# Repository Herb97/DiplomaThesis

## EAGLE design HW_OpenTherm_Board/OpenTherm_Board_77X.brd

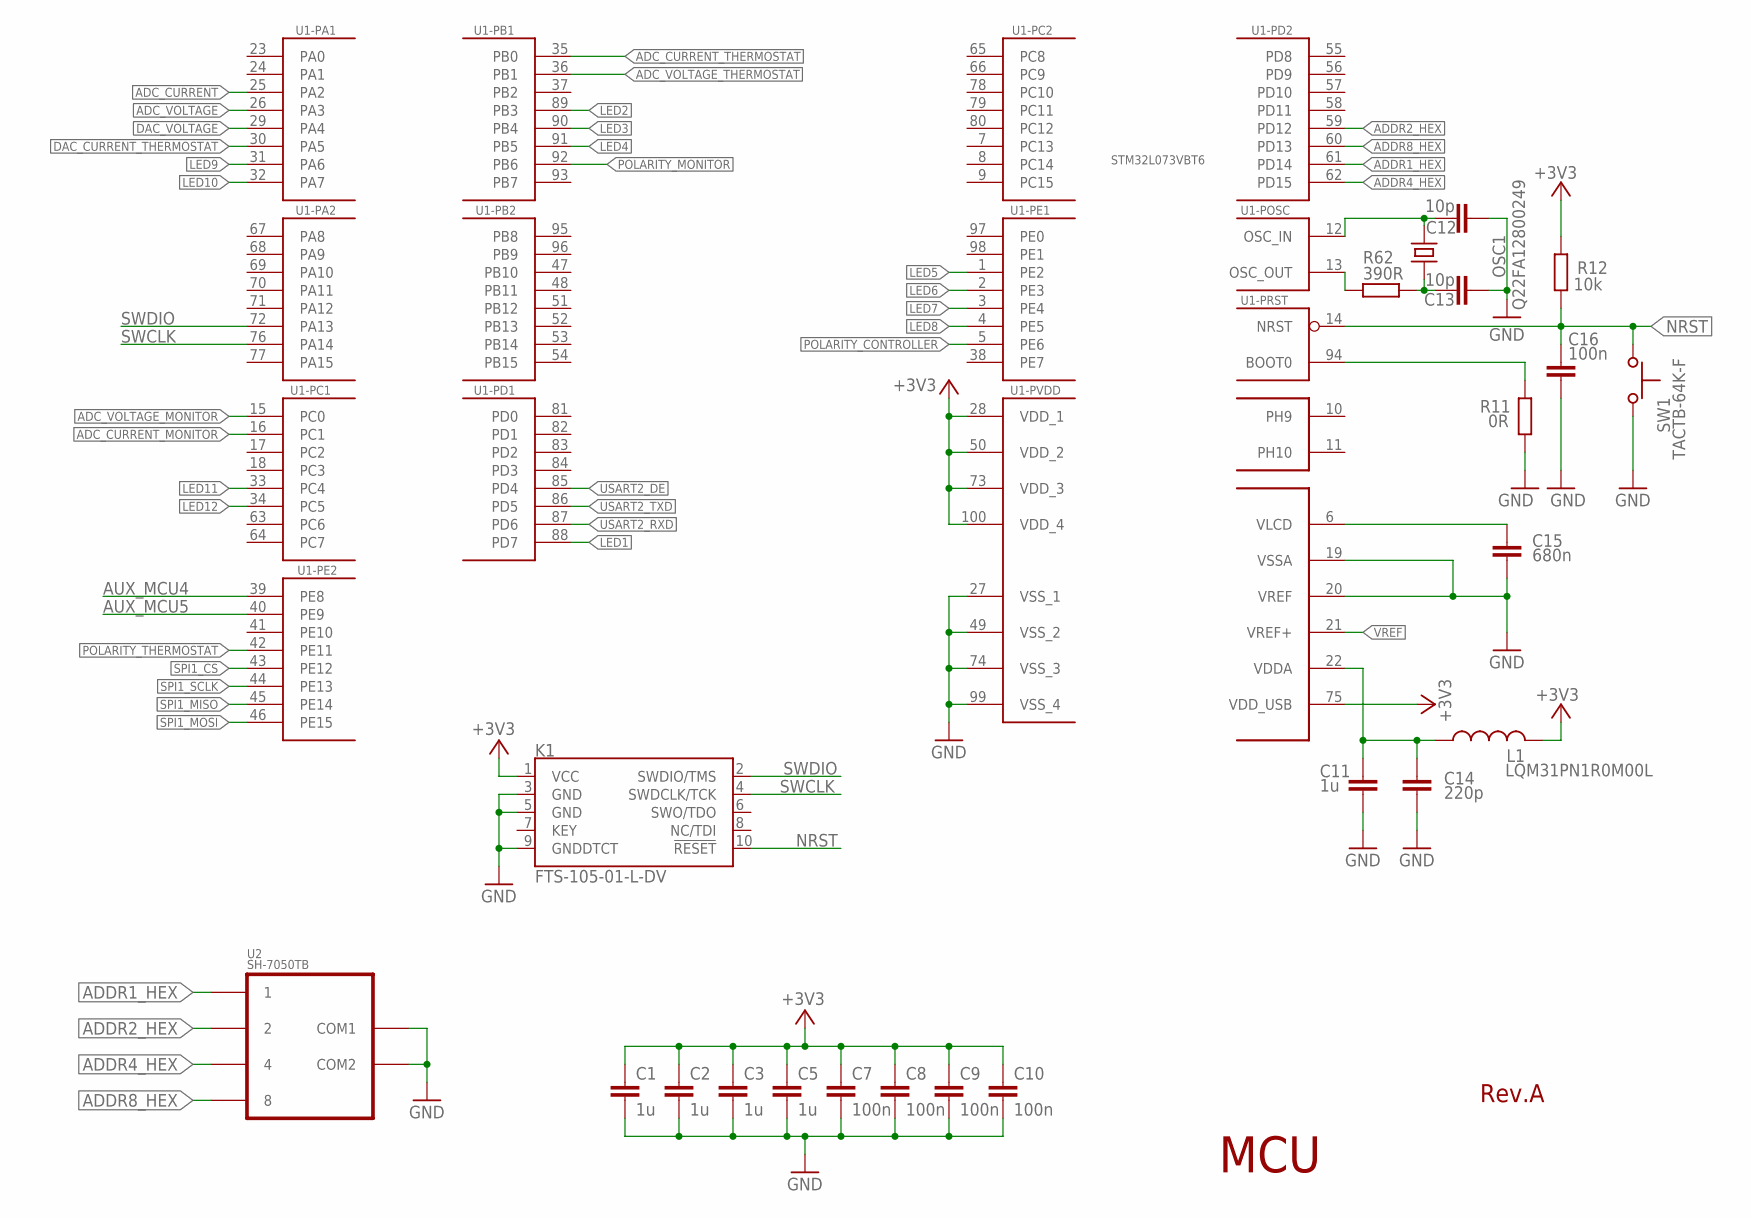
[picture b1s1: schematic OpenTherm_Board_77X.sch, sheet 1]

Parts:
C1, C2, C3, C5, C11: 1u; C0805
C7, C8, C9, C10, C16: 100n; C0603
C12, C13: 10p; C0603
C14: 220p; C0603
C15: 680n; C0603:1
K1: FTS-105-01-L-DV; SAMTECH_FTSH-105-01
L1: LQM31PN1R0M00L; R1206
OSC1: Q22FA12800249; OSCILATOR
R11: 0R; R0603
R12: 10k; R0603
R62: 390R; R0603
SW1: TACTB-64K-F
U1: STM32L073VBT6; TQFP100
U2: SH-7050TB; HEX_DEC

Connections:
+3V3: C1.1, C2.1, C3.1, C5.1, C7.1, C8.1, C9.1, C10.1, K1.1 (VCC), L1.2, R12.2, U1.28 (VDD_1), U1.50 (VDD_2), U1.73 (VDD_3), U1.75 (VDD_USB), U1.100 (VDD_4); also elsewhere on the board
ADC_CURRENT: U1.25 (PA2); also elsewhere on the board
ADC_CURRENT_MONITOR: U1.16 (PC1); also elsewhere on the board
ADC_CURRENT_THERMOSTAT: U1.35 (PB0); also elsewhere on the board
ADC_VOLTAGE: U1.26 (PA3); also elsewhere on the board
ADC_VOLTAGE_MONITOR: U1.15 (PC0); also elsewhere on the board
ADC_VOLTAGE_THERMOSTAT: U1.36 (PB1); also elsewhere on the board
ADDR1_HEX: U1.61 (PD14), U2.1
ADDR2_HEX: U1.59 (PD12), U2.2
ADDR4_HEX: U1.62 (PD15), U2.4
ADDR8_HEX: U1.60 (PD13), U2.8
AUX_MCU4: U1.39 (PE8)
AUX_MCU5: U1.40 (PE9)
BOOT: R11.2, U1.94 (BOOT0)
DAC_CURRENT_THERMOSTAT: U1.30 (PA5); also elsewhere on the board
DAC_VOLTAGE: U1.29 (PA4); also elsewhere on the board
GND: C1.2, C2.2, C3.2, C5.2, C7.2, C8.2, C9.2, C10.2, C11.2, C12.2, C13.2, C14.2, C15.2, C16.2, K1.3 (GND), K1.5 (GND), K1.9 (GNDDTCT), R11.1, SW1.3 (2), U1.19 (VSSA), U1.20 (VREF), U1.27 (VSS_1), U1.49 (VSS_2), U1.74 (VSS_3), U1.99 (VSS_4), U2.C1 (COM1), U2.C2 (COM2); also elsewhere on the board
LED1: U1.88 (PD7); also elsewhere on the board
LED2: U1.89 (PB3); also elsewhere on the board
LED3: U1.90 (PB4); also elsewhere on the board
LED4: U1.91 (PB5); also elsewhere on the board
LED5: U1.1 (PE2); also elsewhere on the board
LED6: U1.2 (PE3); also elsewhere on the board
LED7: U1.3 (PE4); also elsewhere on the board
LED8: U1.4 (PE5); also elsewhere on the board
LED9: U1.31 (PA6); also elsewhere on the board
LED10: U1.32 (PA7); also elsewhere on the board
LED11: U1.33 (PC4); also elsewhere on the board
LED12: U1.34 (PC5); also elsewhere on the board
unnamed: C15.1, U1.6 (VLCD)
NRST: C16.1, K1.10 (!RESET), R12.1, SW1.1, U1.14 (NRST)
OSC: C13.1, OSC1.3, R62.1
OSC+: C12.1, OSC1.1, U1.12 (OSC_IN)
OSC-: R62.2, U1.13 (OSC_OUT)
POLARITY_CONTROLLER: U1.5 (PE6); also elsewhere on the board
POLARITY_MONITOR: U1.92 (PB6); also elsewhere on the board
POLARITY_THERMOSTAT: U1.42 (PE11); also elsewhere on the board
SPI1_CS: U1.43 (PE12)
SPI1_MISO: U1.45 (PE14)
SPI1_MOSI: U1.46 (PE15)
SPI1_SCLK: U1.44 (PE13)
SWCLK: K1.4 (SWDCLK/TCK), U1.76 (PA14)
SWDIO: K1.2 (SWDIO/TMS), U1.72 (PA13)
USART2_DE: U1.85 (PD4); also elsewhere on the board
USART2_RXD: U1.87 (PD6); also elsewhere on the board
USART2_TXD: U1.86 (PD5); also elsewhere on the board
VDDA: C11.1, C14.1, L1.1, U1.22 (VDDA)
VREF: U1.21 (VREF+); also elsewhere on the board

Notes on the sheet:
Rev.A
MCU

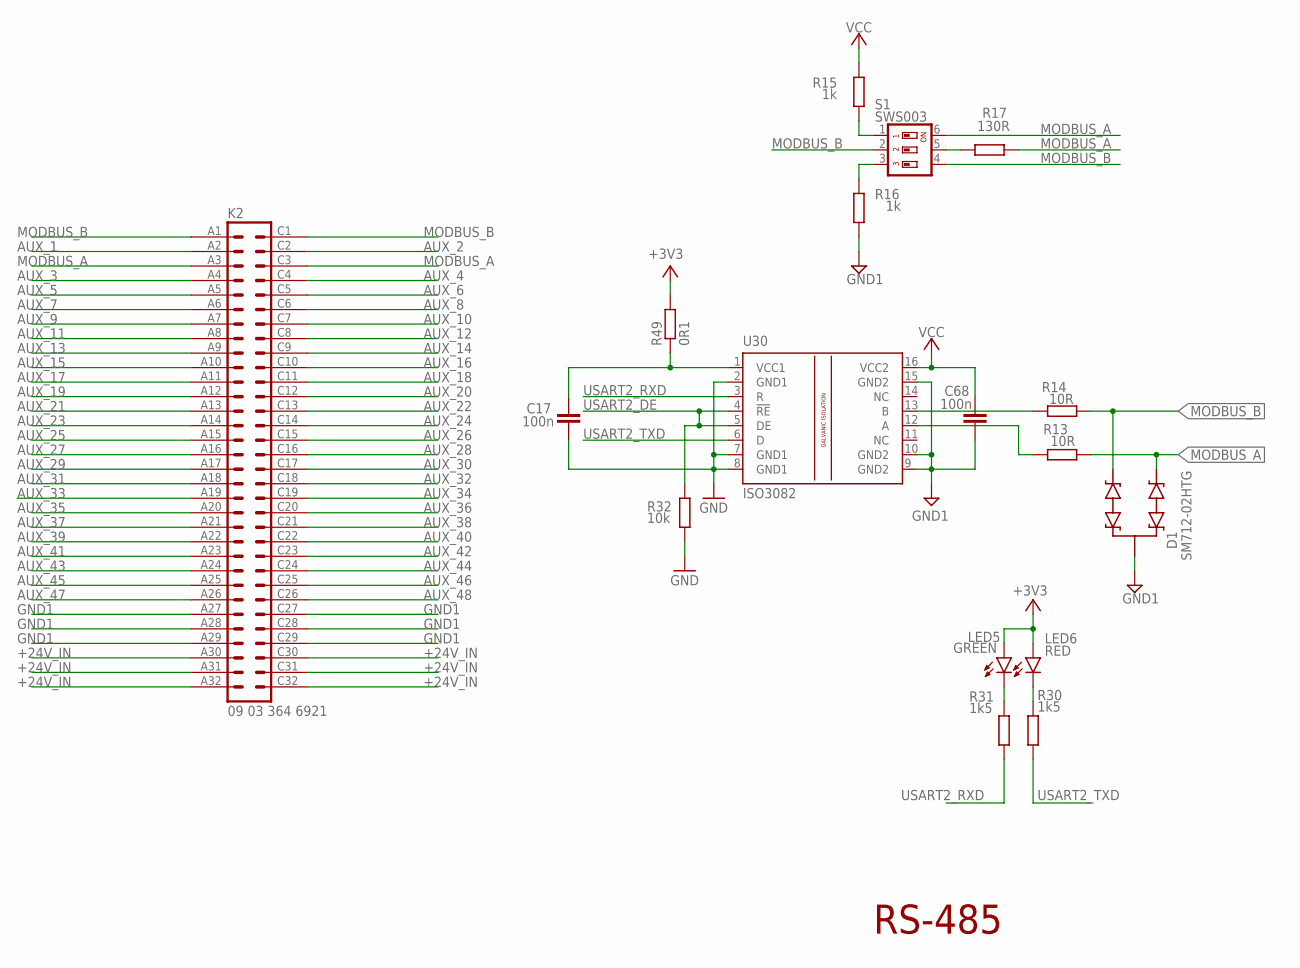
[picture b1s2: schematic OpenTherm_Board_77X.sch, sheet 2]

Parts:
C17, C68: 100n; C0805
D1: SM712-02HTG; SOT23-BEC
K2: 09 03 364 6921; VG64P
LED5: GREEN; CHIPLED_1206
LED6: RED; CHIPLED_1206
R13, R14: 10R; R0603
R15, R16: 1k; R1206
R17: 130R; R1206
R30, R31: 1k5; R1206
R32: 10k; R0603
R49: 0R1; R1206
S1: SWS003; SMS-003
U30: ISO3082; SO-16DW

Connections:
+3V3: LED5.A, LED6.A, R49.2; also elsewhere on the board
+24V_IN: K2.A30, K2.A31, K2.A32, K2.C30, K2.C31, K2.C32; also elsewhere on the board
AUX_1: K2.A2
AUX_2: K2.C2
AUX_3: K2.A4
AUX_4: K2.C4
AUX_5: K2.A5
AUX_6: K2.C5
AUX_7: K2.A6
AUX_8: K2.C6
AUX_9: K2.A7
AUX_10: K2.C7
AUX_11: K2.A8
AUX_12: K2.C8
AUX_13: K2.A9
AUX_14: K2.C9
AUX_15: K2.A10
AUX_16: K2.C10
AUX_17: K2.A11
AUX_18: K2.C11
AUX_19: K2.A12
AUX_20: K2.C12
AUX_21: K2.A13
AUX_22: K2.C13
AUX_23: K2.A14
AUX_24: K2.C14
AUX_25: K2.A15
AUX_26: K2.C15
AUX_27: K2.A16
AUX_28: K2.C16
AUX_29: K2.A17
AUX_30: K2.C17
AUX_31: K2.A18
AUX_32: K2.C18
AUX_33: K2.A19
AUX_34: K2.C19
AUX_35: K2.A20
AUX_36: K2.C20
AUX_37: K2.A21
AUX_38: K2.C21
AUX_39: K2.A22
AUX_40: K2.C22
AUX_41: K2.A23
AUX_42: K2.C23
AUX_43: K2.A24
AUX_44: K2.C24
AUX_45: K2.A25
AUX_46: K2.C25
AUX_47: K2.A26
AUX_48: K2.C26
GND: C17.2, R32.1, U30.2 (GND1), U30.7 (GND1), U30.8 (GND1); also elsewhere on the board
GND1: C68.2, D1.C (E), K2.A27, K2.A28, K2.A29, K2.C27, K2.C28, K2.C29, R16.1, U30.9 (GND2), U30.10 (GND2), U30.15 (GND2); also elsewhere on the board
MODBUS_A: D1.E (2), K2.A3, K2.C3, R13.1, R17.1, S1.6
MODBUS_B: D1.B (1), K2.A1, K2.C1, R14.1, S1.2, S1.4
unnamed: R14.2, U30.13 (B)
unnamed: LED5.C, R31.1
unnamed: R13.2, U30.12 (A)
unnamed: R15.1, S1.1
unnamed: R16.2, S1.3
unnamed: R17.2, S1.5
unnamed: LED6.C, R30.1
unnamed: C17.1, R49.1, U30.1 (VCC1)
USART2_DE: R32.2, U30.4 (!RE), U30.5 (DE); also elsewhere on the board
USART2_RXD: R31.2, U30.3 (R); also elsewhere on the board
USART2_TXD: R30.2, U30.6 (D); also elsewhere on the board
VCC: C68.1, R15.2, U30.16 (VCC2); also elsewhere on the board

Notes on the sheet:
RS-485

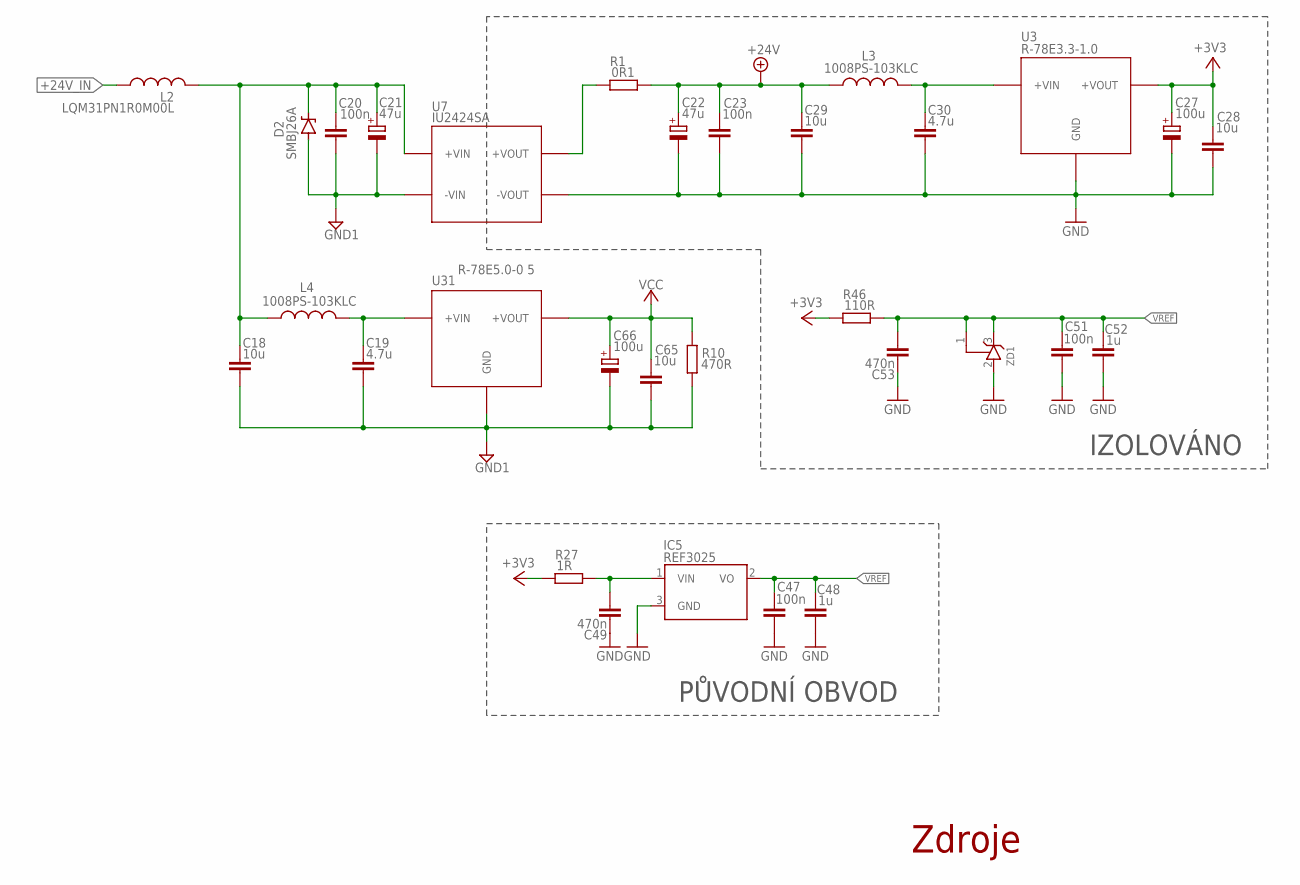
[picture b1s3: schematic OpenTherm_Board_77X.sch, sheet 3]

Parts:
C18, C28, C29, C65: 10u; C1206
C19, C30: 4.7u; C1206
C20: 100n; C1206
C21: 47u; E3,5-8
C22: 47u; 153CLV-0810
C23, C47, C51: 100n; C0805
C27, C66: 100u; 153CLV-0605
C48, C52: 1u; C0805
C49, C53: 470n; C0805
D2: SMBJ26A; SMB
IC5: REF3025; SOT23
L2: LQM31PN1R0M00L; R1206
L3, L4: 1008PS-103KLC; L1812
R1: 0R1; R1206
R10: 470R; R1206
R27: 1R; R0805
R46: 110R; R0805
U3: R-78E3.3-1.0; R-78E-0.5
U7: IU2424SA; IU2405SA
U31: R-78E5.0-0 5; R-78E-0.5
ZD1: TL431INLINE; TO92-R

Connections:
+3V3: C27.+, C28.1, R27.1, R46.1, U3.3 (+VOUT); also elsewhere on the board
+24V: C22.+, C23.1, C29.1, L3.1, R1.2; also elsewhere on the board
+24V_IN: L2.1; also elsewhere on the board
GND: C22.-, C23.2, C27.-, C28.2, C29.2, C30.2, C47.2, C48.2, C49.1, C51.2, C52.2, C53.1, IC5.3 (GND), U3.2 (GND), U7.VOUT- (-VOUT), ZD1.2 (A); also elsewhere on the board
GND1: C18.2, C19.2, C20.2, C21.-, C65.2, C66.-, D2.A, R10.1, U7.VIN- (-VIN), U31.2 (GND); also elsewhere on the board
unnamed: C18.1, C20.1, C21.+, D2.C, L2.2, L4.1, U7.VIN+ (+VIN)
unnamed: C30.1, L3.2, U3.1 (+VIN)
unnamed: C49.2, IC5.1 (VIN), R27.2
unnamed: R1.1, U7.VOUT+ (+VOUT)
unnamed: C19.1, L4.2, U31.1 (+VIN)
VCC: C65.1, C66.+, R10.2, U31.3 (+VOUT); also elsewhere on the board
VREF: C47.1, C48.1, C51.1, C52.1, C53.2, IC5.2 (VO), R46.2, ZD1.1 (R), ZD1.3 (C); also elsewhere on the board

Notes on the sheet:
Zdroje
R-78E5.0-0 5
IU2424SA
R-78E3.3-1.0
IZOLOVÁNO
PŮVODNÍ OBVOD

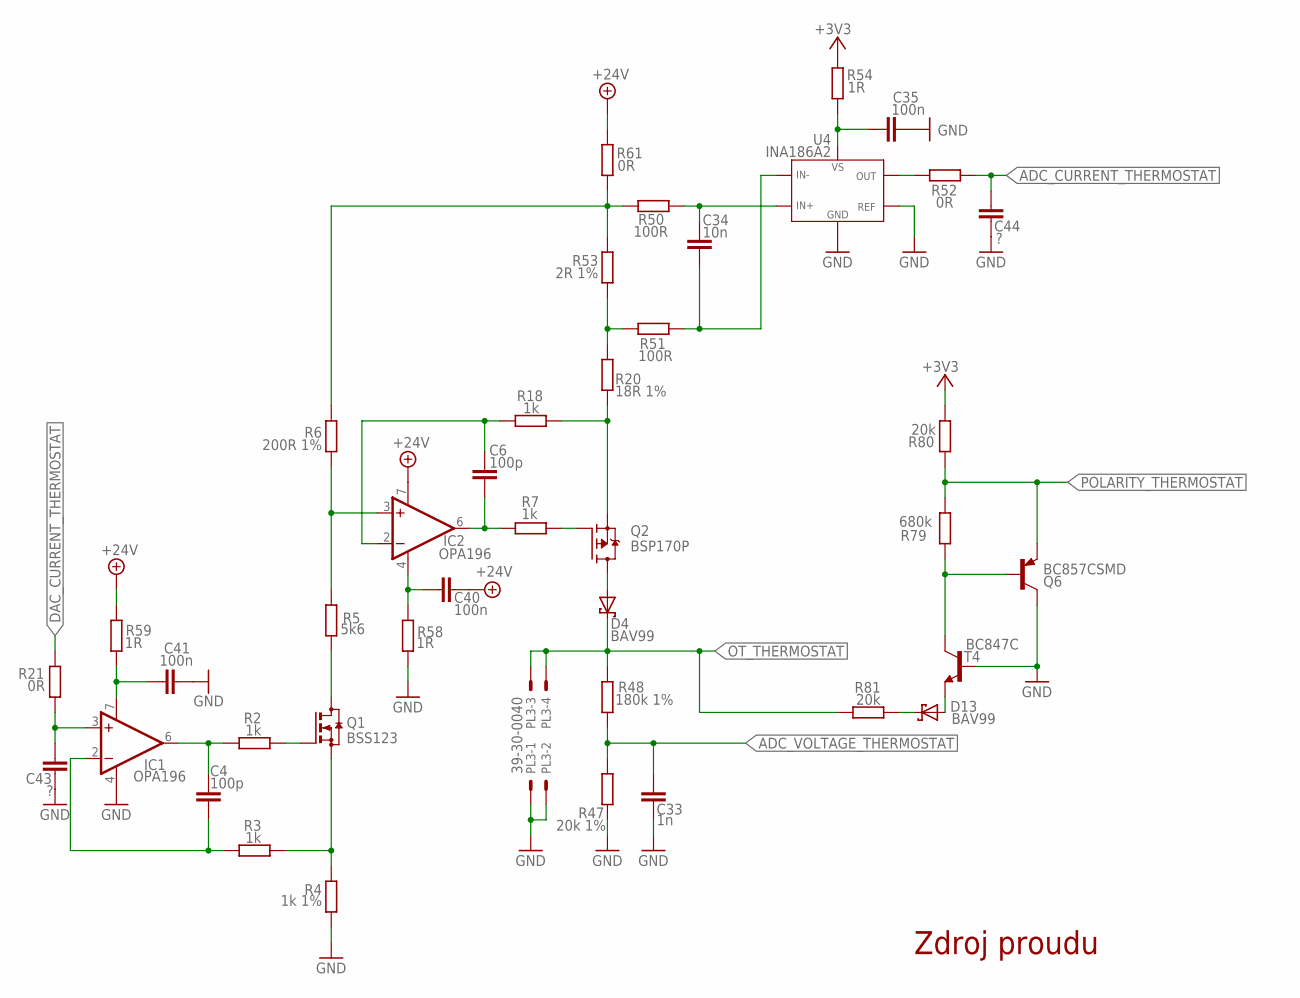
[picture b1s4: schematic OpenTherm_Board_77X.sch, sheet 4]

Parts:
C4, C6: 100p; C0805
C33: 1n; C0805
C34: 10n; C0805
C35, C40, C41: 100n; C0805
C43, C44: ?; C0805
D4, D13: BAV99; SOT23
IC1, IC2: OPA196; SO08
PL3: 39-30-0040; 5569-4
Q1: BSS123; SOT23
Q2: BSP170P; SOT223
Q6: BC857CSMD; SOT23-BEC
R2, R3, R7, R18: 1k; R0805
R4: 1k 1%; R0805
R5: 5k6; R0805
R6: 200R 1%; R0805
R20: 18R 1%; R1206
R21, R52, R61: 0R; R1206
R47: 20k 1%; R0805
R48: 180k 1%; R0805
R50, R51: 100R; R0805
R53: 2R 1%; R1206
R54, R58, R59: 1R; R0805
R79: 680k; R0805
R80, R81: 20k; R0805
T4: BC847C; SOT23
U4: INA186A2; SC70-6L

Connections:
+3V3: R54.2, R80.1; also elsewhere on the board
+24V: C40.1, IC2.7 (V+), R59.2, R61.2; also elsewhere on the board
ADC_CURRENT_THERMOSTAT: C44.1, R52.2; also elsewhere on the board
ADC_VOLTAGE_THERMOSTAT: C33.1, R47.2, R48.1; also elsewhere on the board
DAC_CURRENT_THERMOSTAT: R21.1; also elsewhere on the board
GND: C33.2, C35.2, C41.2, C43.1, C44.2, IC1.4 (V-), PL3.1, PL3.2, Q6.C, R4.1, R47.1, R58.1, T4.1 (B), U4.1 (REF), U4.2 (GND); also elsewhere on the board
unnamed: IC2.3 (+IN), R5.2, R6.1
unnamed: Q1.3 (D), R5.1
unnamed: D4.1 (A), Q2.2 (D), Q2.4 (D)
unnamed: Q1.2 (S), R3.2, R4.2
unnamed: Q1.1 (G), R2.2
unnamed: C4.1, IC1.6 (OUT), R2.1
unnamed: C4.2, IC1.2 (-IN), R3.1
unnamed: C6.2, IC2.6 (OUT), R7.1
unnamed: C6.1, IC2.2 (-IN), R18.1
unnamed: Q2.3 (S), R18.2, R20.1
unnamed: Q2.1 (G), R7.2
unnamed: C43.2, IC1.3 (+IN), R21.2
unnamed: R6.2, R50.1, R53.2, R61.1
unnamed: C34.1, R50.2, U4.4 (IN+)
unnamed: C34.2, R51.2, U4.5 (IN-)
unnamed: R20.2, R51.1, R53.1
unnamed: R52.1, U4.6 (OUT)
unnamed: C35.1, R54.1, U4.3 (VS)
unnamed: C40.2, IC2.4 (V-), R58.2
unnamed: C41.1, IC1.7 (V+), R59.1
unnamed: Q6.B, R79.2, T4.3 (C)
unnamed: D13.1 (A), T4.2 (E)
unnamed: D13.3 (C), R81.1
OT_THERMOSTAT: D4.3 (C), PL3.3, PL3.4, R48.2, R81.2
POLARITY_THERMOSTAT: Q6.E, R79.1, R80.2; also elsewhere on the board

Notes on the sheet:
Zdroj proudu

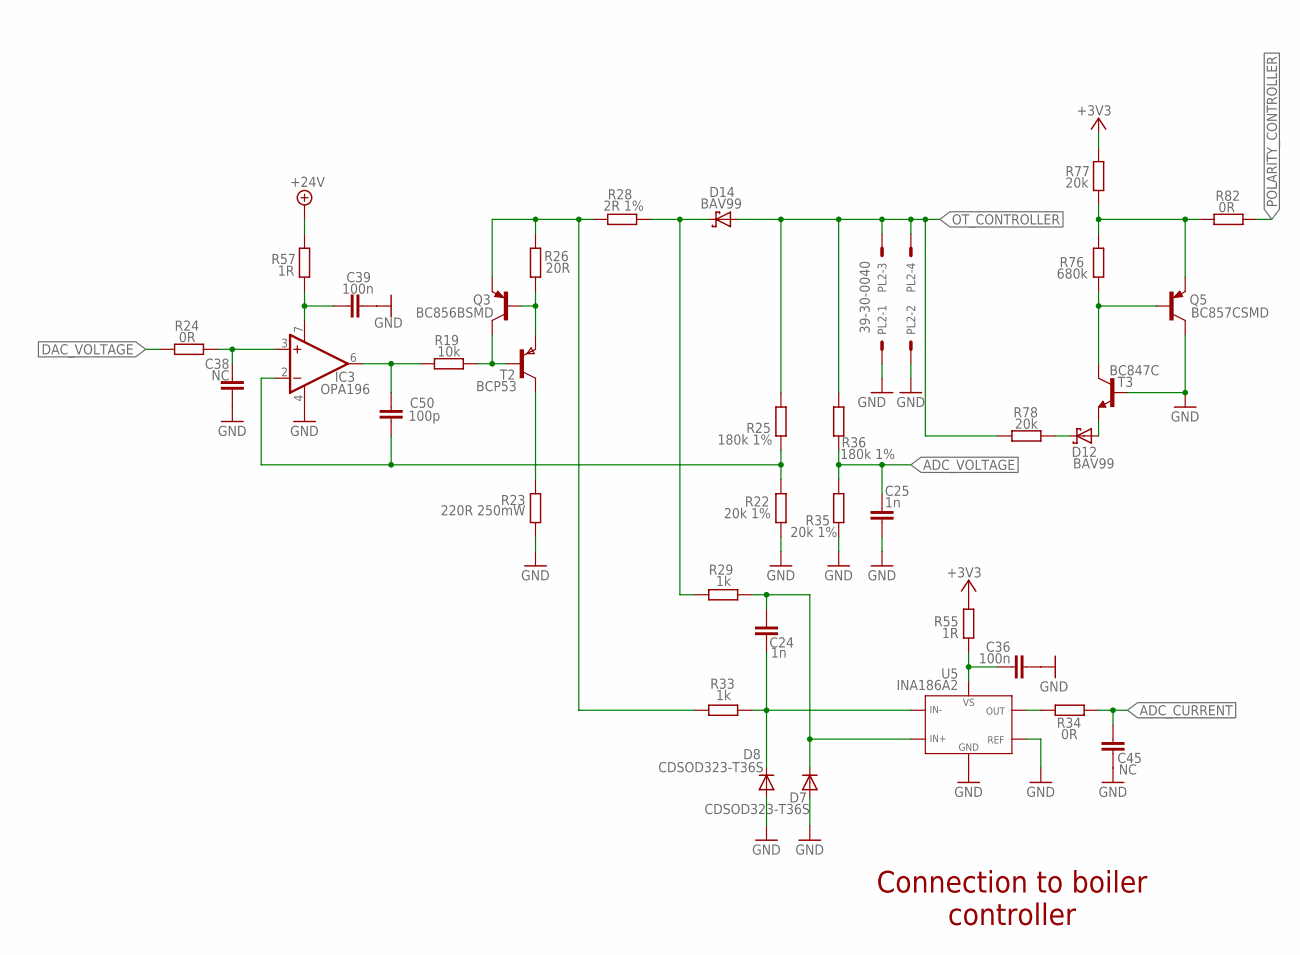
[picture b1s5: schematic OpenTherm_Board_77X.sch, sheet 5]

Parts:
C24, C25: 1n; C0805
C36, C39: 100n; C0805
C38, C45: NC; C0805
C50: 100p; C0805
D7, D8: CDSOD323-T36S; SOD323-W
D12, D14: BAV99; SOT23
IC3: OPA196; SO08
PL2: 39-30-0040; 5569-4
Q3: BC856BSMD; SOT23-BEC
Q5: BC857CSMD; SOT23-BEC
R19: 10k; R0805
R22, R35: 20k 1%; R0805
R23: 220R 250mW; R1206
R24, R34, R82: 0R; R1206
R25, R36: 180k 1%; R0805
R26: 20R; R1206
R28: 2R 1%; R1206
R29, R33: 1k; R0805
R55: 1R; R0805
R57: 1R; R1206
R76: 680k; R0805
R77, R78: 20k; R0805
T2: BCP53; SOT223
T3: BC847C; SOT23
U5: INA186A2; SC70-6L

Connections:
+3V3: R55.2, R77.1; also elsewhere on the board
+24V: R57.2; also elsewhere on the board
ADC_CURRENT: C45.1, R34.2; also elsewhere on the board
ADC_VOLTAGE: C25.1, R35.2, R36.1; also elsewhere on the board
DAC_VOLTAGE: R24.1; also elsewhere on the board
GND: C25.2, C36.2, C38.1, C39.2, C45.2, D7.A, D8.A, IC3.4 (V-), PL2.1, PL2.2, Q5.C, R22.1, R23.1, R35.1, T3.1 (B), U5.1 (REF), U5.2 (GND); also elsewhere on the board
unnamed: R23.2, T2.2 (C), T2.4 (C)
unnamed: C50.2, IC3.6 (OUT), R19.1
unnamed: C50.1, IC3.2 (-IN), R22.2, R25.1
unnamed: C38.2, IC3.3 (+IN), R24.2
unnamed: Q3.C, R19.2, T2.1 (B)
unnamed: Q3.B, R26.1, T2.3 (E)
unnamed: Q3.E, R26.2, R28.1, R33.1
unnamed: D14.3 (C), R28.2, R29.1
unnamed: C24.1, D7.C, R29.2, U5.4 (IN+)
unnamed: C24.2, D8.C, R33.2, U5.5 (IN-)
unnamed: Q5.B, R76.2, T3.3 (C)
unnamed: R34.1, U5.6 (OUT)
unnamed: C36.1, R55.1, U5.3 (VS)
unnamed: C39.1, IC3.7 (V+), R57.1
unnamed: D12.1 (A), T3.2 (E)
unnamed: D12.3 (C), R78.1
unnamed: Q5.E, R76.1, R77.2, R82.1
OT_CONTROLLER: D14.1 (A), PL2.3, PL2.4, R25.2, R36.2, R78.2
POLARITY_CONTROLLER: R82.2; also elsewhere on the board

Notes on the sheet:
Connection to boiler controller

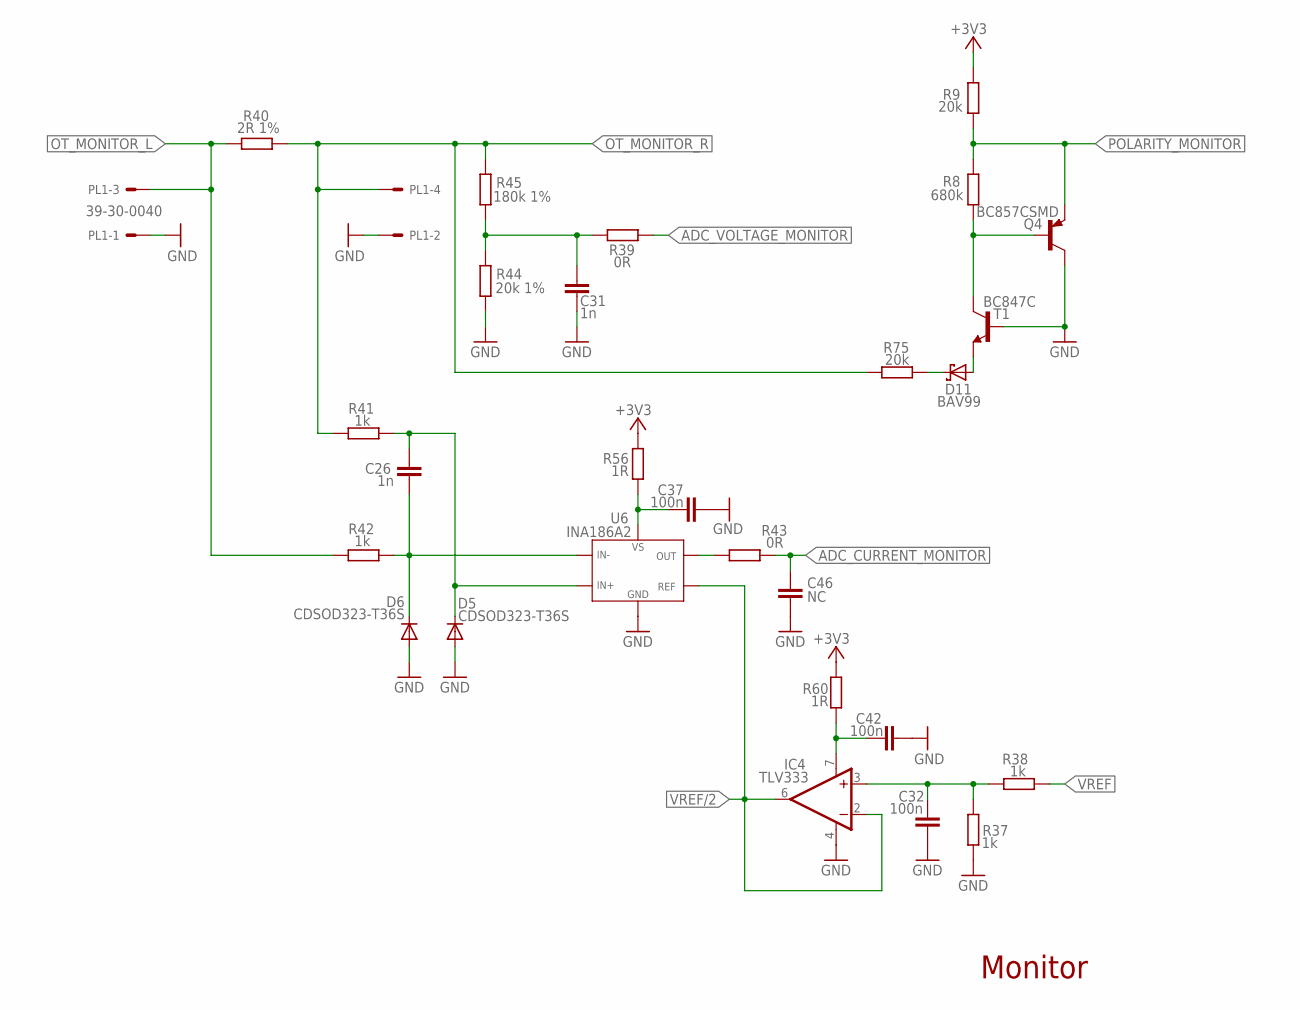
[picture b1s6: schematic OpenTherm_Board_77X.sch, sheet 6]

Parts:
C26, C31: 1n; C0805
C32, C37, C42: 100n; C0805
C46: NC; C0805
D5, D6: CDSOD323-T36S; SOD323-W
D11: BAV99; SOT23
IC4: TLV333; SO08
PL1: 39-30-0040; 5569-4
Q4: BC857CSMD; SOT23-BEC
R8: 680k; R0805
R9, R75: 20k; R0805
R37, R38: 1k; R1206
R39, R43: 0R; R1206
R40: 2R 1%; R1206
R41, R42: 1k; R0805
R44: 20k 1%; R0805
R45: 180k 1%; R0805
R56, R60: 1R; R0805
T1: BC847C; SOT23
U6: INA186A2; SC70-6L

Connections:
+3V3: R9.1, R56.2, R60.2; also elsewhere on the board
ADC_CURRENT_MONITOR: C46.1, R43.2; also elsewhere on the board
ADC_VOLTAGE_MONITOR: R39.2; also elsewhere on the board
GND: C31.2, C32.1, C37.2, C42.2, C46.2, D5.A, D6.A, IC4.4 (V-), PL1.1, PL1.2, Q4.C, R37.1, R44.1, T1.1 (B), U6.2 (GND); also elsewhere on the board
unnamed: C32.2, IC4.3 (+IN), R37.2, R38.1
unnamed: C26.1, D5.C, R41.2, U6.4 (IN+)
unnamed: C26.2, D6.C, R42.2, U6.5 (IN-)
unnamed: R43.1, U6.6 (OUT)
unnamed: C37.1, R56.1, U6.3 (VS)
unnamed: C42.1, IC4.7 (V+), R60.1
unnamed: Q4.B, R8.2, T1.3 (C)
unnamed: D11.1 (A), T1.2 (E)
unnamed: D11.3 (C), R75.1
unnamed: C31.1, R39.1, R44.2, R45.1
OT_MONITOR_L: PL1.3, R40.1, R42.1
OT_MONITOR_R: PL1.4, R40.2, R41.1, R45.2, R75.2
POLARITY_MONITOR: Q4.E, R8.1, R9.2; also elsewhere on the board
VREF: R38.2; also elsewhere on the board
VREF/2: IC4.2 (-IN), IC4.6 (OUT), U6.1 (REF)

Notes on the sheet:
Monitor

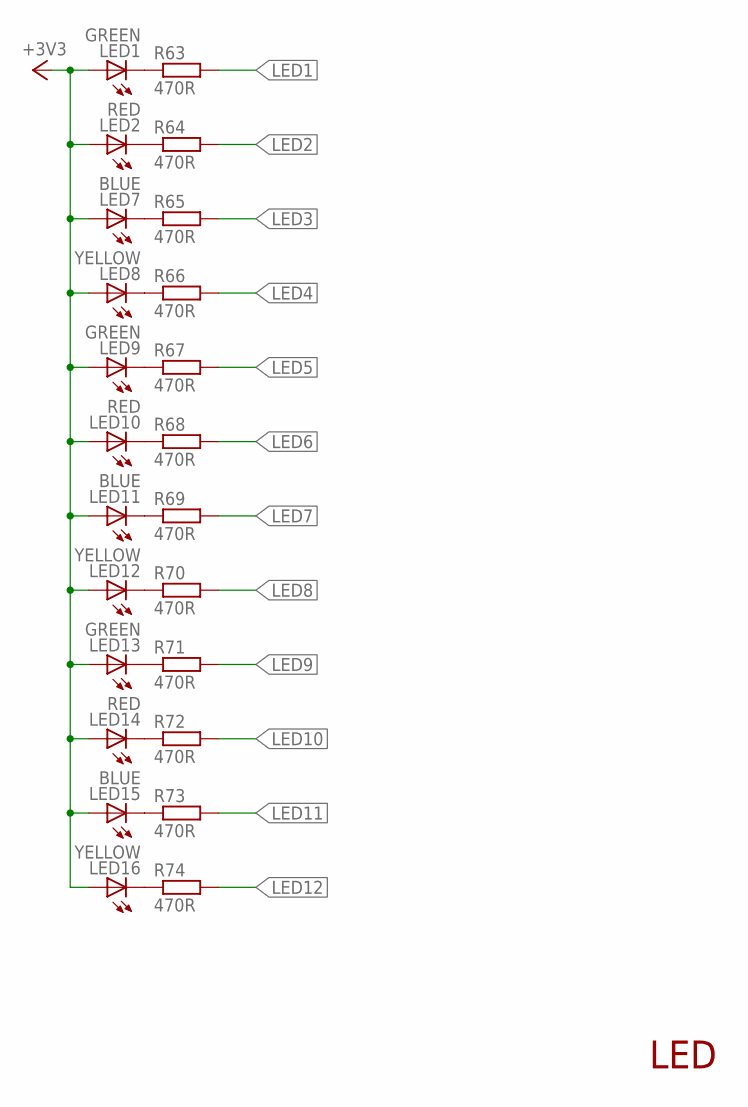
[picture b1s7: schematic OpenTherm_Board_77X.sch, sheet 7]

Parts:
LED1, LED9, LED13: GREEN; LED3MM
LED2, LED10, LED14: RED; LED3MM
LED7, LED11, LED15: BLUE; LED3MM
LED8, LED12, LED16: YELLOW; LED3MM
R63, R64, R65, R66, R67, R68, R69, R70, R71, R72, R73, R74: 470R; R1206

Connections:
+3V3: LED1.A, LED2.A, LED7.A, LED8.A, LED9.A, LED10.A, LED11.A, LED12.A, LED13.A, LED14.A, LED15.A, LED16.A; also elsewhere on the board
LED1: R63.2; also elsewhere on the board
LED2: R64.2; also elsewhere on the board
LED3: R65.2; also elsewhere on the board
LED4: R66.2; also elsewhere on the board
LED5: R67.2; also elsewhere on the board
LED6: R68.2; also elsewhere on the board
LED7: R69.2; also elsewhere on the board
LED8: R70.2; also elsewhere on the board
LED9: R71.2; also elsewhere on the board
LED10: R72.2; also elsewhere on the board
LED11: R73.2; also elsewhere on the board
LED12: R74.2; also elsewhere on the board
unnamed: LED1.K (C), R63.1
unnamed: LED2.K (C), R64.1
unnamed: LED7.K (C), R65.1
unnamed: LED8.K (C), R66.1
unnamed: LED9.K (C), R67.1
unnamed: LED10.K (C), R68.1
unnamed: LED11.K (C), R69.1
unnamed: LED12.K (C), R70.1
unnamed: LED13.K (C), R71.1
unnamed: LED14.K (C), R72.1
unnamed: LED15.K (C), R73.1
unnamed: LED16.K (C), R74.1

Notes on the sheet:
LED

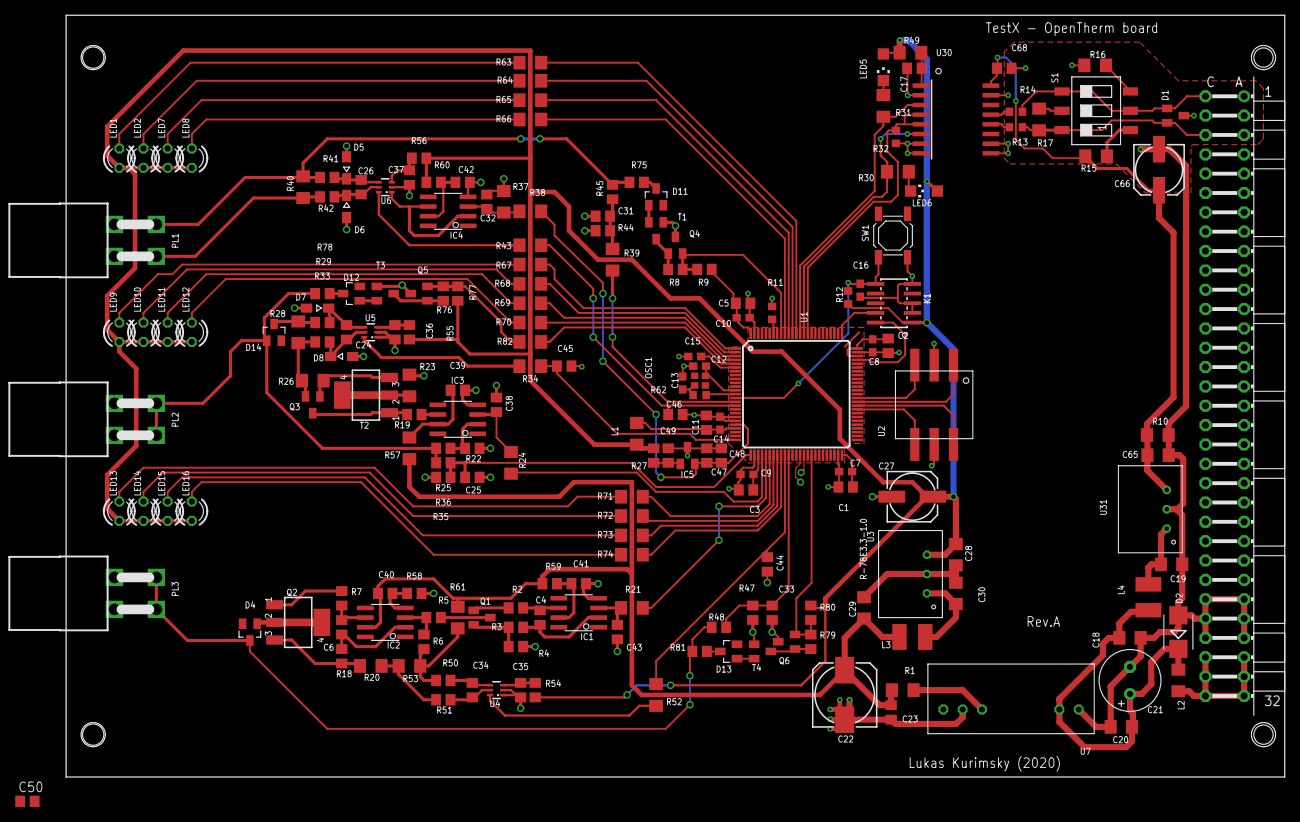
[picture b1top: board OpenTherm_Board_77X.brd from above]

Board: 2 copper layers, 160.0 x 100.0 mm, 195 parts (0 on the bottom side), 128 nets.

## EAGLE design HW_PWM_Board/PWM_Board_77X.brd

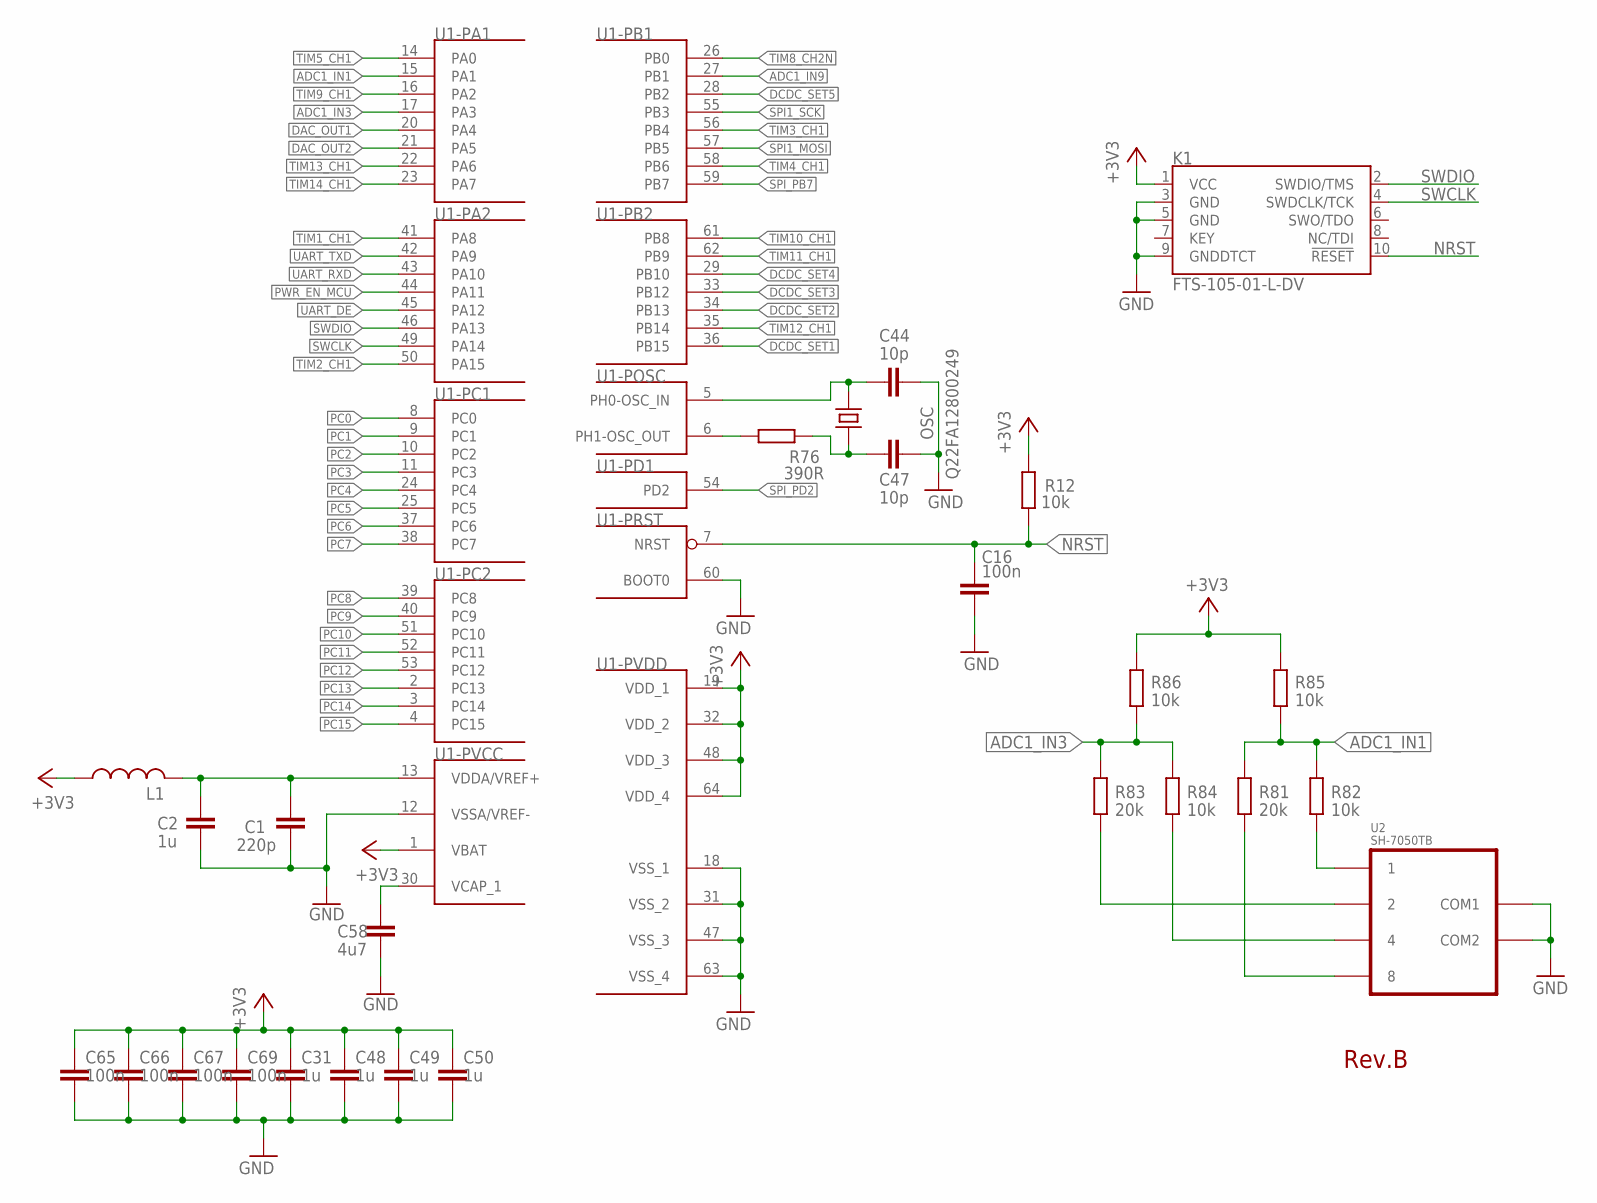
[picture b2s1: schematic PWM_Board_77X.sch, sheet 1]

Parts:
C1: 220p; C0603
C2, C31, C48, C49, C50: 1u; C0805
C16: 100n; C0603
C44, C47: 10p; C0603
C58: 4u7; C0805
C65, C66, C67, C69: 100n; C0805
K1: FTS-105-01-L-DV; SAMTECH_FTSH-105-01
L1: L-US; R1206
OSC: Q22FA12800249; OSCILATOR
R12, R82, R84, R85, R86: 10k; R0603
R76: 390R; R0603
R81, R83: 20k; R0603
U1: STM32F446RE_64PIN; LQFP64_F446RE
U2: SH-7050TB; HEX_DEC

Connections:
+3V3: C31.1, C48.1, C49.1, C50.1, C65.1, C66.1, C67.1, C69.1, K1.1 (VCC), L1.1, R12.2, R85.1, R86.1, U1.1 (VBAT), U1.19 (VDD_1), U1.32 (VDD_2), U1.48 (VDD_3), U1.64 (VDD_4); also elsewhere on the board
ADC1_IN1: R81.1, R82.1, R85.2, U1.15 (PA1)
ADC1_IN3: R83.1, R84.1, R86.2, U1.17 (PA3)
ADC1_IN9: U1.27 (PB1); also elsewhere on the board
DAC_OUT1: U1.20 (PA4); also elsewhere on the board
DAC_OUT2: U1.21 (PA5); also elsewhere on the board
DCDC_SET1: U1.36 (PB15); also elsewhere on the board
DCDC_SET2: U1.34 (PB13); also elsewhere on the board
DCDC_SET3: U1.33 (PB12); also elsewhere on the board
DCDC_SET4: U1.29 (PB10); also elsewhere on the board
DCDC_SET5: U1.28 (PB2); also elsewhere on the board
GND: C1.2, C2.2, C16.2, C31.2, C44.1, C47.1, C48.2, C49.2, C50.2, C58.2, C65.2, C66.2, C67.2, C69.2, K1.3 (GND), K1.5 (GND), K1.9 (GNDDTCT), U1.12 (VSSA/VREF-), U1.18 (VSS_1), U1.31 (VSS_2), U1.47 (VSS_3), U1.60 (BOOT0), U1.63 (VSS_4), U2.C1 (COM1), U2.C2 (COM2); also elsewhere on the board
unnamed: R81.2, U2.8
unnamed: R83.2, U2.2
unnamed: C58.1, U1.30 (VCAP_1)
unnamed: R84.2, U2.4
unnamed: R82.2, U2.1
NRST: C16.1, K1.10 (!RESET), R12.1, U1.7 (NRST)
OSC: C47.2, OSC.3, R76.2
OSC_IN: C44.2, OSC.1, U1.5 (PH0-OSC_IN)
OSC_OUT: R76.1, U1.6 (PH1-OSC_OUT)
PC0: U1.8 (PC0); also elsewhere on the board
PC1: U1.9 (PC1); also elsewhere on the board
PC2: U1.10 (PC2); also elsewhere on the board
PC3: U1.11 (PC3); also elsewhere on the board
PC4: U1.24 (PC4); also elsewhere on the board
PC5: U1.25 (PC5); also elsewhere on the board
PC6: U1.37 (PC6); also elsewhere on the board
PC7: U1.38 (PC7); also elsewhere on the board
PC8: U1.39 (PC8); also elsewhere on the board
PC9: U1.40 (PC9); also elsewhere on the board
PC10: U1.51 (PC10); also elsewhere on the board
PC11: U1.52 (PC11); also elsewhere on the board
PC12: U1.53 (PC12); also elsewhere on the board
PC13: U1.2 (PC13); also elsewhere on the board
PC14: U1.3 (PC14); also elsewhere on the board
PC15: U1.4 (PC15); also elsewhere on the board
PWR_EN_MCU: U1.44 (PA11); also elsewhere on the board
SPI1_MOSI: U1.57 (PB5); also elsewhere on the board
SPI1_SCK: U1.55 (PB3); also elsewhere on the board
SPI_PB7: U1.59 (PB7); also elsewhere on the board
SPI_PD2: U1.54 (PD2); also elsewhere on the board
SWCLK: K1.4 (SWDCLK/TCK), U1.49 (PA14)
SWDIO: K1.2 (SWDIO/TMS), U1.46 (PA13)
TIM1_CH1: U1.41 (PA8); also elsewhere on the board
TIM2_CH1: U1.50 (PA15); also elsewhere on the board
TIM3_CH1: U1.56 (PB4); also elsewhere on the board
TIM4_CH1: U1.58 (PB6); also elsewhere on the board
TIM5_CH1: U1.14 (PA0); also elsewhere on the board
TIM8_CH2N: U1.26 (PB0); also elsewhere on the board
TIM9_CH1: U1.16 (PA2); also elsewhere on the board
TIM10_CH1: U1.61 (PB8); also elsewhere on the board
TIM11_CH1: U1.62 (PB9); also elsewhere on the board
TIM12_CH1: U1.35 (PB14); also elsewhere on the board
TIM13_CH1: U1.22 (PA6); also elsewhere on the board
TIM14_CH1: U1.23 (PA7); also elsewhere on the board
UART_DE: U1.45 (PA12); also elsewhere on the board
UART_RXD: U1.43 (PA10); also elsewhere on the board
UART_TXD: U1.42 (PA9); also elsewhere on the board
VREF+: C1.1, C2.1, L1.2, U1.13 (VDDA/VREF+)

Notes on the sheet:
Rev.B

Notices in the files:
parts and their libraries:
praxe: Copyright (C)
